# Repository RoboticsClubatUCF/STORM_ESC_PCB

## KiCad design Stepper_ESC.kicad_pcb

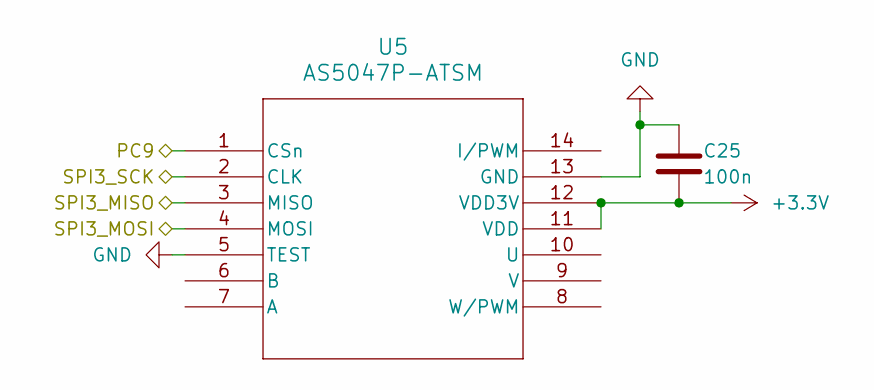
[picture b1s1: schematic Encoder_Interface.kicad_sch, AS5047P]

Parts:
C25: 100n; C_0402_1005Metric
U5: AS5047P-ATSM; TSSOP14_OSM

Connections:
/CAN_Interface/CAN_ENABLE: U5.6 (EN); also elsewhere on the board
/CAN_Interface/CAN_FAULT: U5.8 (FAULT_N); also elsewhere on the board
/CAN_Interface/CAN_STANDBY: U5.14 (STB_N); also elsewhere on the board
/CAN_Interface/FDCAN1_RX: U5.1 (TXD); also elsewhere on the board
/CAN_Interface/FDCAN1_TX: U5.4 (RXD); also elsewhere on the board
unnamed 161: U5.9 (WAKE); also elsewhere on the board

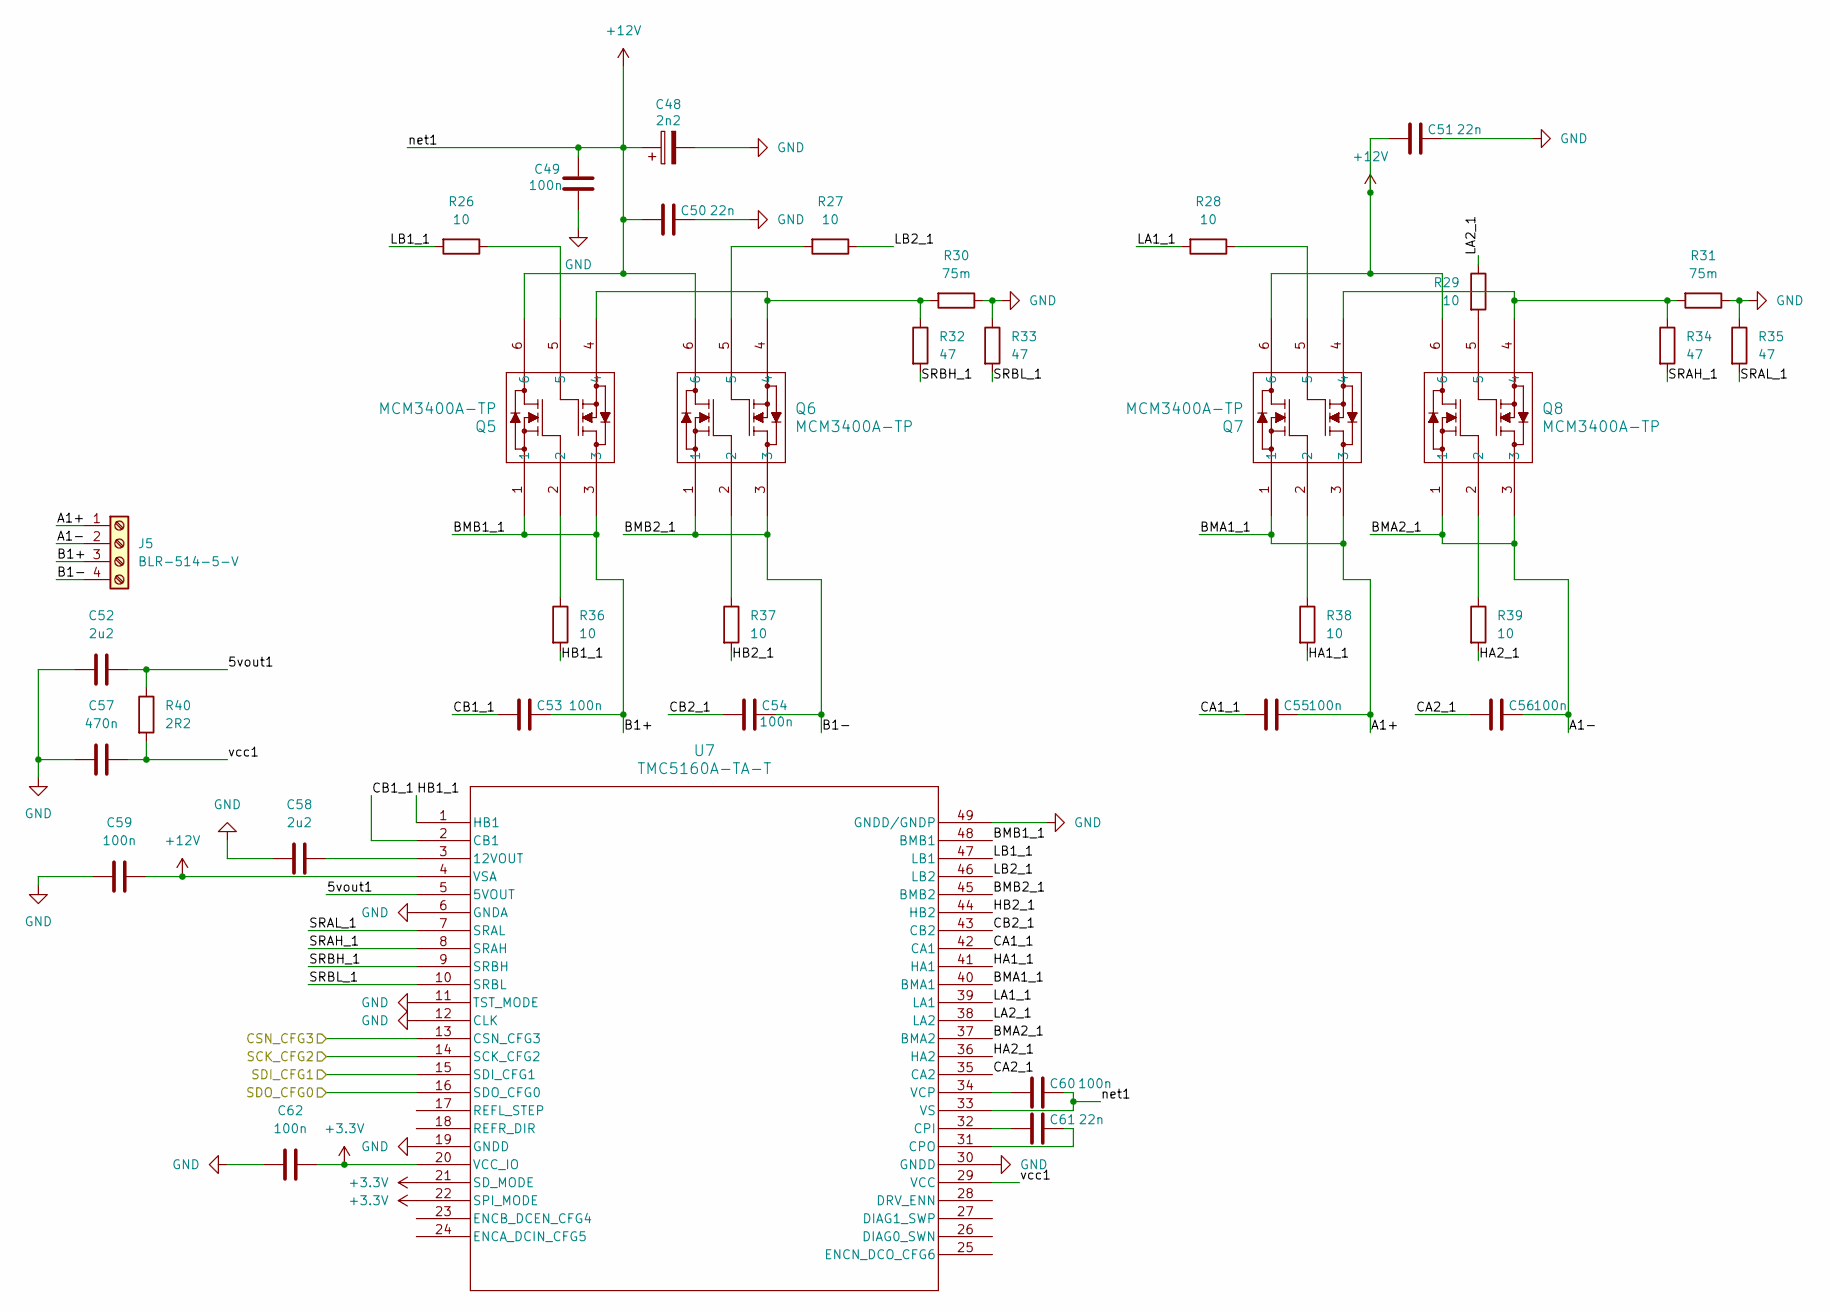
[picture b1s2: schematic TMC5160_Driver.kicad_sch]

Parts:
C48: 2n2; CP_Radial_D10.0mm_P5.00mm
C49, C53, C54, C55, C56, C59, C60, C62: 100n; C_0402_1005Metric
C50, C51, C61: 22n; C_0402_1005Metric
C52, C58: 2u2; C_0402_1005Metric
C57: 470n; C_0402_1005Metric
J5: BLR-514-5-V; TerminalBlock_Dinkle_DT-55-B01X-04_P10.00mm
Q5, Q6, Q7, Q8: MCM3400A-TP; DFN2020-6L_MCE
R26, R27, R28, R29, R36, R37, R38, R39: 10; R_0402_1005Metric
R30, R31: 75m; R_0402_1005Metric
R32, R33, R34, R35: 47; R_0402_1005Metric
R40: 2R2; R_0402_1005Metric
U7: TMC5160A-TA-T; 21-100582_ADI

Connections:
+12V: C48.1, C49.1, C50.2, C51.2, C59.1, C60.1, Q5.6, Q6.6, Q7.6, Q8.6, U7.4 (VSA), U7.33 (VS); also elsewhere on the board
/MCU_STM32/CSN_CFG3: U7.13 (CSN_CFG3); also elsewhere on the board
/MCU_STM32/SCK_CFG2: U7.14 (SCK_CFG2); also elsewhere on the board
/MCU_STM32/SDI_CFG1: U7.15 (SDI_CFG1); also elsewhere on the board
/MCU_STM32/SDO_CFG0: U7.16 (SDO_CFG0); also elsewhere on the board
/TMC5160_Driver1/5vout1: C52.1, R40.1, U7.5 (5VOUT)
/TMC5160_Driver1/A1+: C55.1, J5.1, Q7.1, Q7.3, U7.40 (BMA1)
/TMC5160_Driver1/A1-: C56.1, J5.2, Q8.1, Q8.3, U7.37 (BMA2)
/TMC5160_Driver1/B1+: C53.1, J5.3, Q5.1, Q5.3, U7.48 (BMB1)
/TMC5160_Driver1/B1-: C54.1, J5.4, Q6.1, Q6.3, U7.45 (BMB2)
/TMC5160_Driver1/CA1_1: C55.2, U7.42 (CA1)
/TMC5160_Driver1/CA2_1: C56.2, U7.35 (CA2)
/TMC5160_Driver1/CB1_1: C53.2, U7.2 (CB1)
/TMC5160_Driver1/CB2_1: C54.2, U7.43 (CB2)
/TMC5160_Driver1/HA1_1: R38.2, U7.41 (HA1)
/TMC5160_Driver1/HA2_1: R39.2, U7.36 (HA2)
/TMC5160_Driver1/HB1_1: R36.2, U7.1 (HB1)
/TMC5160_Driver1/HB2_1: R37.2, U7.44 (HB2)
/TMC5160_Driver1/LA1_1: R28.2, U7.39 (LA1)
/TMC5160_Driver1/LA2_1: R29.1, U7.38 (LA2)
/TMC5160_Driver1/LB1_1: R26.2, U7.47 (LB1)
/TMC5160_Driver1/LB2_1: R27.1, U7.46 (LB2)
/TMC5160_Driver1/SRAH_1: R34.2, U7.8 (SRAH)
/TMC5160_Driver1/SRAL_1: R35.2, U7.7 (SRAL)
/TMC5160_Driver1/SRBH_1: R32.2, U7.9 (SRBH)
/TMC5160_Driver1/SRBL_1: R33.2, U7.10 (SRBL)
/TMC5160_Driver1/vcc1: C57.1, R40.2, U7.29 (VCC)
unnamed: Q5.2, R36.1
unnamed: Q5.4, Q6.4, R30.2, R32.1
unnamed: Q5.5, R26.1
unnamed: Q6.2, R37.1
unnamed: Q6.5, R27.2
unnamed: Q7.2, R38.1
unnamed: Q7.4, Q8.4, R31.2, R34.1
unnamed: Q7.5, R28.1
unnamed: Q8.2, R39.1
unnamed: Q8.5, R29.2
unnamed: C58.1, U7.3 (12VOUT)
unnamed: C61.2, U7.32 (CPI)
unnamed: C61.1, U7.31 (CPO)
unnamed: C60.2, U7.34 (VCP)

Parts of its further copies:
C63, C78, C93: 2n2; CP_Radial_D10.0mm_P5.00mm
C64, C68, C69, C70, C71, C74, C75, C77, C79, C83, C84, C85, C86, C89, C90, C92, C94, C98, C99, C100, C101, C104, C105, C107: 100n; C_0402_1005Metric
C65, C66, C76, C80, C81, C91, C95, C96, C106: 22n; C_0402_1005Metric
C67, C73, C82, C88, C97, C103: 2u2; C_0402_1005Metric
C72, C87, C102: 470n; C_0402_1005Metric
J6, J7, J8: BLR-514-5-V; TerminalBlock_Dinkle_DT-55-B01X-04_P10.00mm
Q9, Q10, Q11, Q12, Q13, Q14, Q15, Q16, Q17, Q18, Q19, Q20: MCM3400A-TP; DFN2020-6L_MCE
R41, R42, R43, R44, R51, R52, R53, R54, R56, R57, R58, R59, R66, R67, R68, R69, R71, R72, R73, R74, R81, R82, R83, R84: 10; R_0402_1005Metric
R45, R46, R60, R61, R75, R76: 75m; R_0402_1005Metric
R47, R48, R49, R50, R62, R63, R64, R65, R77, R78, R79, R80: 47; R_0402_1005Metric
R55, R70, R85: 2R2; R_0402_1005Metric
U8, U9, U10: TMC5160A-TA-T; 21-100582_ADI

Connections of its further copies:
+12V: C63.1, C64.1, C65.2, C66.2, C74.1, C75.1, C78.1, C79.1, C80.2, C81.2, C89.1, C90.1, C93.1, C94.1, C95.2, C96.2, C104.1, C105.1, Q9.6, Q10.6, Q11.6, Q12.6, Q13.6, Q14.6, Q15.6, Q16.6, Q17.6, Q18.6, Q19.6, Q20.6, U8.4 (VSA), U8.33 (VS), U9.4 (VSA), U9.33 (VS), U10.4 (VSA), U10.33 (VS); also elsewhere on the board
/MCU_STM32/CSN_CFG3: U8.13 (CSN_CFG3), U9.13 (CSN_CFG3), U10.13 (CSN_CFG3); also elsewhere on the board
/MCU_STM32/SCK_CFG2: U8.14 (SCK_CFG2), U9.14 (SCK_CFG2), U10.14 (SCK_CFG2); also elsewhere on the board
/MCU_STM32/SDI_CFG1: U8.15 (SDI_CFG1), U9.15 (SDI_CFG1), U10.15 (SDI_CFG1); also elsewhere on the board
/MCU_STM32/SDO_CFG0: U8.16 (SDO_CFG0), U9.16 (SDO_CFG0), U10.16 (SDO_CFG0); also elsewhere on the board
/TMC5160_Driver2/5vout1: C67.1, R55.1, U8.5 (5VOUT)
/TMC5160_Driver2/A1+: C70.1, J6.1, Q11.1, Q11.3, U8.40 (BMA1)
/TMC5160_Driver2/A1-: C71.1, J6.2, Q12.1, Q12.3, U8.37 (BMA2)
/TMC5160_Driver2/B1+: C68.1, J6.3, Q9.1, Q9.3, U8.48 (BMB1)
/TMC5160_Driver2/B1-: C69.1, J6.4, Q10.1, Q10.3, U8.45 (BMB2)
/TMC5160_Driver2/CA1_1: C70.2, U8.42 (CA1)
/TMC5160_Driver2/CA2_1: C71.2, U8.35 (CA2)
/TMC5160_Driver2/CB1_1: C68.2, U8.2 (CB1)
/TMC5160_Driver2/CB2_1: C69.2, U8.43 (CB2)
/TMC5160_Driver2/HA1_1: R53.2, U8.41 (HA1)
/TMC5160_Driver2/HA2_1: R54.2, U8.36 (HA2)
/TMC5160_Driver2/HB1_1: R51.2, U8.1 (HB1)
/TMC5160_Driver2/HB2_1: R52.2, U8.44 (HB2)
/TMC5160_Driver2/LA1_1: R43.2, U8.39 (LA1)
/TMC5160_Driver2/LA2_1: R44.1, U8.38 (LA2)
/TMC5160_Driver2/LB1_1: R41.2, U8.47 (LB1)
/TMC5160_Driver2/LB2_1: R42.1, U8.46 (LB2)
/TMC5160_Driver2/SRAH_1: R49.2, U8.8 (SRAH)
/TMC5160_Driver2/SRAL_1: R50.2, U8.7 (SRAL)
/TMC5160_Driver2/SRBH_1: R47.2, U8.9 (SRBH)
/TMC5160_Driver2/SRBL_1: R48.2, U8.10 (SRBL)
/TMC5160_Driver2/vcc1: C72.1, R55.2, U8.29 (VCC)
/TMC5160_Driver3/5vout1: C82.1, R70.1, U9.5 (5VOUT)
/TMC5160_Driver3/A1+: C85.1, J7.1, Q15.1, Q15.3, U9.40 (BMA1)
/TMC5160_Driver3/A1-: C86.1, J7.2, Q16.1, Q16.3, U9.37 (BMA2)
/TMC5160_Driver3/B1+: C83.1, J7.3, Q13.1, Q13.3, U9.48 (BMB1)
/TMC5160_Driver3/B1-: C84.1, J7.4, Q14.1, Q14.3, U9.45 (BMB2)
/TMC5160_Driver3/CA1_1: C85.2, U9.42 (CA1)
/TMC5160_Driver3/CA2_1: C86.2, U9.35 (CA2)
/TMC5160_Driver3/CB1_1: C83.2, U9.2 (CB1)
/TMC5160_Driver3/CB2_1: C84.2, U9.43 (CB2)
/TMC5160_Driver3/HA1_1: R68.2, U9.41 (HA1)
/TMC5160_Driver3/HA2_1: R69.2, U9.36 (HA2)
/TMC5160_Driver3/HB1_1: R66.2, U9.1 (HB1)
/TMC5160_Driver3/HB2_1: R67.2, U9.44 (HB2)
/TMC5160_Driver3/LA1_1: R58.2, U9.39 (LA1)
/TMC5160_Driver3/LA2_1: R59.1, U9.38 (LA2)
/TMC5160_Driver3/LB1_1: R56.2, U9.47 (LB1)
/TMC5160_Driver3/LB2_1: R57.1, U9.46 (LB2)
/TMC5160_Driver3/SRAH_1: R64.2, U9.8 (SRAH)
/TMC5160_Driver3/SRAL_1: R65.2, U9.7 (SRAL)
/TMC5160_Driver3/SRBH_1: R62.2, U9.9 (SRBH)
/TMC5160_Driver3/SRBL_1: R63.2, U9.10 (SRBL)
/TMC5160_Driver3/vcc1: C87.1, R70.2, U9.29 (VCC)
/TMC5160_Driver4/5vout1: C97.1, R85.1, U10.5 (5VOUT)
/TMC5160_Driver4/A1+: C100.1, J8.1, Q19.1, Q19.3, U10.40 (BMA1)
/TMC5160_Driver4/A1-: C101.1, J8.2, Q20.1, Q20.3, U10.37 (BMA2)
/TMC5160_Driver4/B1+: C98.1, J8.3, Q17.1, Q17.3, U10.48 (BMB1)
/TMC5160_Driver4/B1-: C99.1, J8.4, Q18.1, Q18.3, U10.45 (BMB2)
/TMC5160_Driver4/CA1_1: C100.2, U10.42 (CA1)
/TMC5160_Driver4/CA2_1: C101.2, U10.35 (CA2)
/TMC5160_Driver4/CB1_1: C98.2, U10.2 (CB1)
/TMC5160_Driver4/CB2_1: C99.2, U10.43 (CB2)
/TMC5160_Driver4/HA1_1: R83.2, U10.41 (HA1)
/TMC5160_Driver4/HA2_1: R84.2, U10.36 (HA2)
/TMC5160_Driver4/HB1_1: R81.2, U10.1 (HB1)
/TMC5160_Driver4/HB2_1: R82.2, U10.44 (HB2)
/TMC5160_Driver4/LA1_1: R73.2, U10.39 (LA1)
/TMC5160_Driver4/LA2_1: R74.1, U10.38 (LA2)
/TMC5160_Driver4/LB1_1: R71.2, U10.47 (LB1)
/TMC5160_Driver4/LB2_1: R72.1, U10.46 (LB2)
/TMC5160_Driver4/SRAH_1: R79.2, U10.8 (SRAH)
/TMC5160_Driver4/SRAL_1: R80.2, U10.7 (SRAL)
/TMC5160_Driver4/SRBH_1: R77.2, U10.9 (SRBH)
/TMC5160_Driver4/SRBL_1: R78.2, U10.10 (SRBL)
/TMC5160_Driver4/vcc1: C102.1, R85.2, U10.29 (VCC)
unnamed: Q9.2, R51.1
unnamed: Q9.5, R41.1
unnamed: Q10.2, R52.1
unnamed: Q9.4, Q10.4, R45.2, R47.1
unnamed: Q10.5, R42.2
unnamed: Q11.2, R53.1
unnamed: Q11.4, Q12.4, R46.2, R49.1
unnamed: Q11.5, R43.1
unnamed: Q12.2, R54.1
unnamed: Q12.5, R44.2
unnamed: Q13.2, R66.1
unnamed: Q13.4, Q14.4, R60.2, R62.1
unnamed: Q13.5, R56.1
unnamed: Q14.2, R67.1
unnamed: Q14.5, R57.2
unnamed: Q15.2, R68.1
unnamed: Q15.4, Q16.4, R61.2, R64.1
unnamed: Q15.5, R58.1
unnamed: Q16.2, R69.1
unnamed: Q16.5, R59.2
unnamed: Q17.2, R81.1
unnamed: Q17.4, Q18.4, R75.2, R77.1
unnamed: Q17.5, R71.1
unnamed: Q18.2, R82.1
unnamed: Q18.5, R72.2
unnamed: Q19.2, R83.1
unnamed: Q19.4, Q20.4, R76.2, R79.1
unnamed: Q19.5, R73.1
unnamed: Q20.2, R84.1
unnamed: Q20.5, R74.2
unnamed: C73.1, U8.3 (12VOUT)
unnamed: C76.2, U8.32 (CPI)
unnamed: C76.1, U8.31 (CPO)
unnamed: C75.2, U8.34 (VCP)
unnamed: C88.1, U9.3 (12VOUT)
unnamed: C91.2, U9.32 (CPI)
unnamed: C91.1, U9.31 (CPO)
unnamed: C90.2, U9.34 (VCP)
unnamed: C103.1, U10.3 (12VOUT)
unnamed: C106.2, U10.32 (CPI)
unnamed: C106.1, U10.31 (CPO)
unnamed: C105.2, U10.34 (VCP)

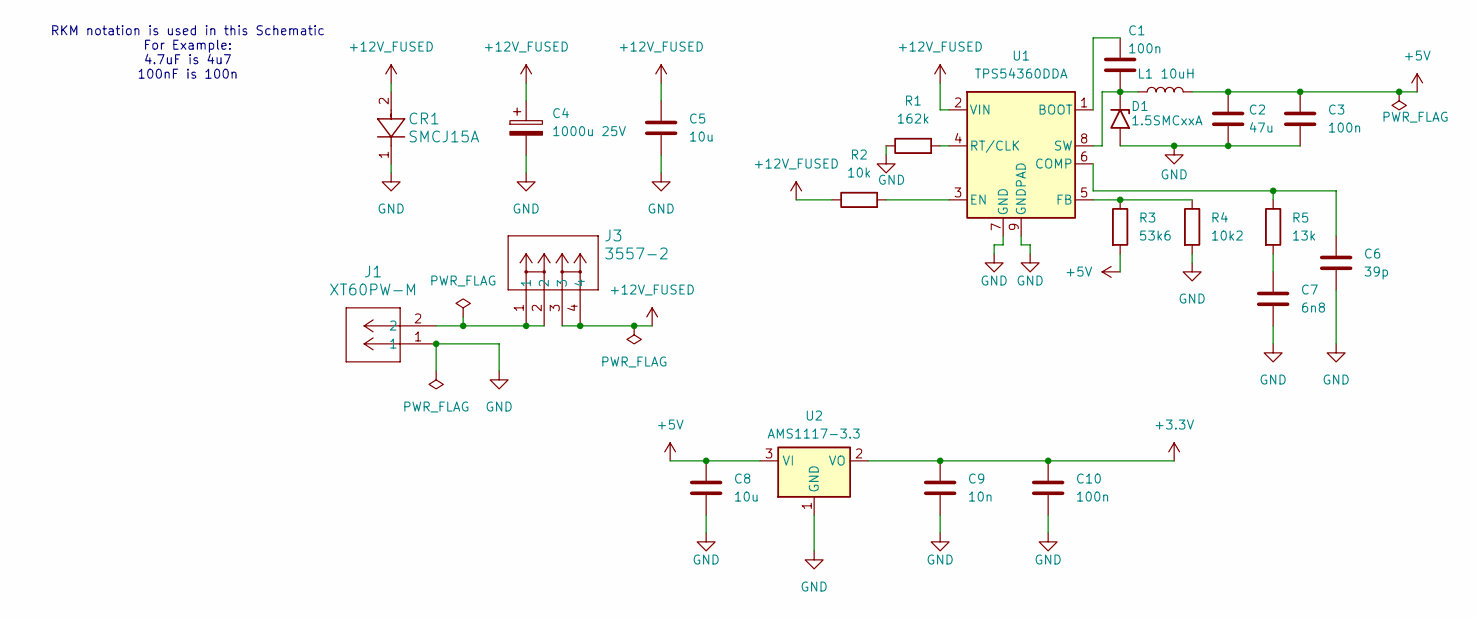
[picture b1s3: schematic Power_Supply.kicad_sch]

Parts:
C1, C3, C10: 100n; C_0402_1005Metric
C2: 47u; C_0402_1005Metric
C4: 1000u 25V; CP_Radial_D10.0mm_P5.00mm
C5: 10u; C_0805_2012Metric
C6: 39p; C_0402_1005Metric
C7: 6n8; C_0402_1005Metric
C8: 10u; C_0402_1005Metric
C9: 10n; C_0402_1005Metric
CR1: SMCJ15A; DIODE_DO-214AC
D1: 1.5SMCxxA; D_SMC
J1: XT60PW-M; CONN_XT60PW-M_AMA
J3: 3557-2; CONN_3557-2_KEY
L1: 10uH; L_Bourns_SRP1245A
R1: 162k; R_0402_1005Metric
R2: 10k; R_0402_1005Metric
R3: 53k6; R_0402_1005Metric
R4: 10k2; R_0402_1005Metric
R5: 13k; R_0402_1005Metric
U1: TPS54360DDA; TI_SO-PowerPAD-8_ThermalVias
U2: AMS1117-3.3; SOT-223-3_TabPin2

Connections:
unnamed: C7.1, R5.2
unnamed: C1.2, D1.1 (A1), L1.1, U1.8 (SW)
unnamed: J1.2, J3.1, J3.2
unnamed: C1.1, U1.1 (BOOT)
unnamed: C6.1, R5.1, U1.6 (COMP)
unnamed: R2.2, U1.3 (EN)
unnamed: R3.1, R4.1, U1.5 (FB)
unnamed: R1.2, U1.4 (RT/CLK)

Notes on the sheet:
RKM notation is used in this Schematic For Example: 4.7uF is 4u7 100nF is 100n

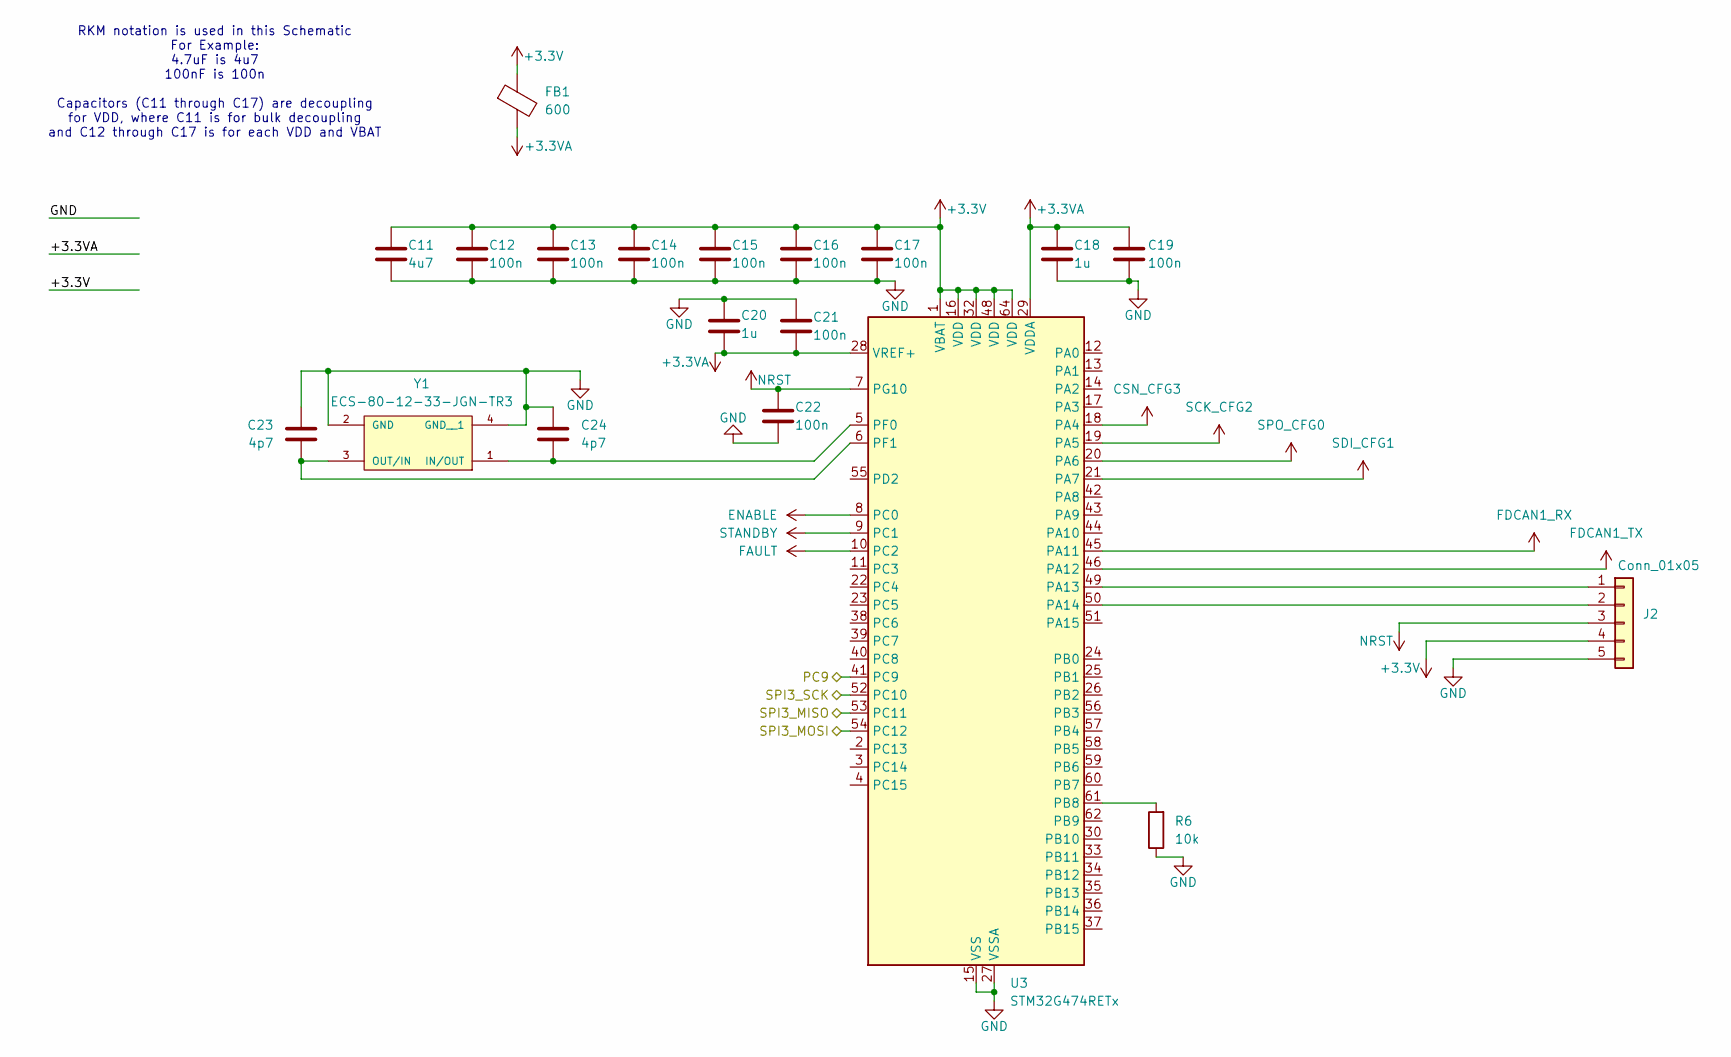
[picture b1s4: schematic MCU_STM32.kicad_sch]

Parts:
C11: 4u7; C_0402_1005Metric
C12, C13, C14, C15, C16, C17, C19, C21, C22: 100n; C_0402_1005Metric
C18, C20: 1u; C_0402_1005Metric
C23, C24: 4p7; C_0402_1005Metric
FB1: 600
J2: Conn_01x05; PinHeader_1x05_P1.00mm_Vertical
R6: 10k; R_0402_1005Metric
U3: STM32G474RETx; LQFP-64_10x10mm_P0.5mm
Y1: ECS-80-12-33-JGN-TR3; XTAL_ECS-240-8-33-AGN-TR

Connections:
+3.3VA: C18.2, C19.2, C20.2, C21.1, FB1.2, U3.28 (VREF+), U3.29 (VDDA)
/AS5047P/PC9: U3.41 (PC9); also elsewhere on the board
/AS5047P/SPI3_MISO: U3.52 (PC10); also elsewhere on the board
/AS5047P/SPI3_MOSI: U3.54 (PC12); also elsewhere on the board
/AS5047P/SPI3_SCK: U3.53 (PC11); also elsewhere on the board
/CAN_Interface/CAN_ENABLE: U3.8 (PC0); also elsewhere on the board
/CAN_Interface/CAN_FAULT: U3.10 (PC2); also elsewhere on the board
/CAN_Interface/CAN_STANDBY: U3.9 (PC1); also elsewhere on the board
/CAN_Interface/FDCAN1_RX: U3.45 (PA11); also elsewhere on the board
/CAN_Interface/FDCAN1_TX: U3.46 (PA12); also elsewhere on the board
/MCU_STM32/CSN_CFG3: U3.18 (PA4); also elsewhere on the board
/MCU_STM32/NRST: C22.2, J2.3, U3.7 (PG10)
/MCU_STM32/SCK_CFG2: U3.19 (PA5); also elsewhere on the board
/MCU_STM32/SDI_CFG1: U3.21 (PA7); also elsewhere on the board
/MCU_STM32/SDO_CFG0: U3.20 (PA6); also elsewhere on the board
unnamed: J2.1, U3.49 (PA13)
unnamed: J2.2, U3.50 (PA14)
unnamed: R6.2, U3.61 (PB8)
unnamed: C24.1, U3.5 (PF0), Y1.1 (IN/OUT)
unnamed: C23.1, U3.6 (PF1), Y1.3 (OUT/IN)

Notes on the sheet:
RKM notation is used in this Schematic For Example: 4.7uF is 4u7 100nF is 100n Capacitors (C11 through C17) are decoupling for VDD, where C11 is for bulk decoupling and C12 through C17 is for each VDD and VBAT

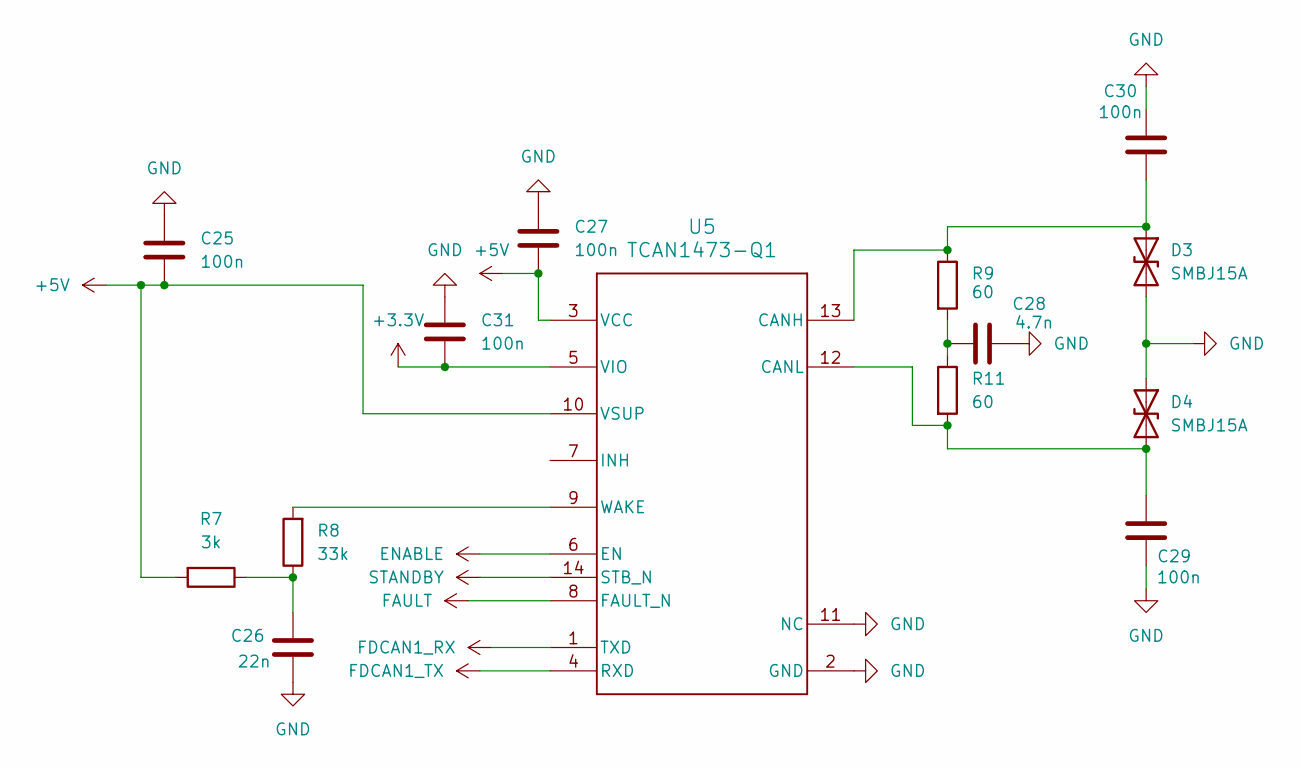
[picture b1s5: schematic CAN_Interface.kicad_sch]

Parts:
C25, C27, C29, C30, C31: 100n; C_0402_1005Metric
C26: 22n; C_0402_1005Metric
C28: 4.7n; C_0402_1005Metric
D3, D4: SMBJ15A
R7: 3k; R_0402_1005Metric
R8: 33k; R_0402_1005Metric
R9, R11: 60
U5: TCAN1473-Q1; D0014A-IPC_B

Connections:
/CAN_Interface/CAN_ENABLE: U5.6 (EN); also elsewhere on the board
/CAN_Interface/CAN_FAULT: U5.8 (FAULT_N); also elsewhere on the board
/CAN_Interface/CAN_STANDBY: U5.14 (STB_N); also elsewhere on the board
/CAN_Interface/FDCAN1_RX: U5.1 (TXD); also elsewhere on the board
/CAN_Interface/FDCAN1_TX: U5.4 (RXD); also elsewhere on the board
unnamed: C26.1, R7.1, R8.1
unnamed: C28.2, R9.2, R11.1
unnamed 161: R8.2, U5.9 (WAKE); also elsewhere on the board

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
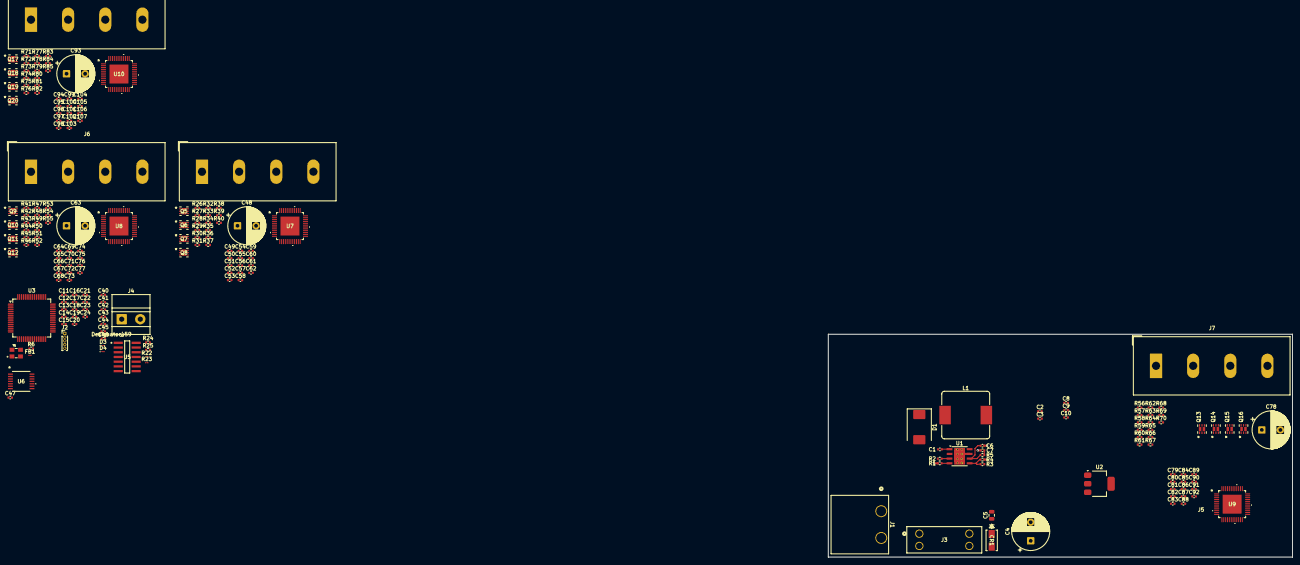
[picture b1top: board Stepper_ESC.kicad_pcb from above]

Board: 4 copper layers, 125.0 x 60.0 mm, 202 parts (0 on the bottom side), 182 nets.

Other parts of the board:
C40, C41, C42, C43, C45, C47: 100n; C_0402_1005Metric
C44: 4.7n; C_0402_1005Metric
C46: 22n; C_0402_1005Metric
J4: Screw_Terminal_01x02; TerminalBlock_MetzConnect_Type011_RT05502HBLC_1x02_P5.00mm_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
R22, R23: 60; R_01005_0402Metric
R24: 33k; R_0402_1005Metric
R25: 3k; R_0402_1005Metric
U6: AS5047P-ATSM; TSSOP14_OSM

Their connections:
/AS5047P/PC9: U6.1 (CSn); also elsewhere on the board
/AS5047P/SPI3_MISO: U6.3 (MISO); also elsewhere on the board
/AS5047P/SPI3_MOSI: U6.4 (MOSI); also elsewhere on the board
/AS5047P/SPI3_SCK: U6.2 (CLK); also elsewhere on the board
unnamed: C44.2, R22.2, R23.1
unnamed: C46.1, R24.1, R25.1
unnamed 161: R24.2; also elsewhere on the board
